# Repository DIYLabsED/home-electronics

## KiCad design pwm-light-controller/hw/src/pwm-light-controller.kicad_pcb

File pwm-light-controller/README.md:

## NAME
### DESC

### REQUIREMENTS

### DESIGN NOTES

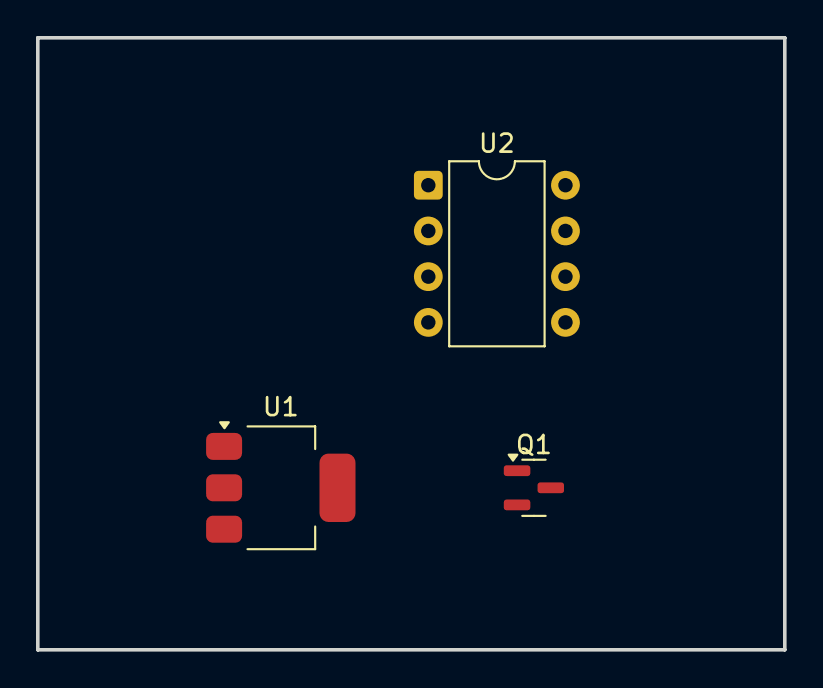
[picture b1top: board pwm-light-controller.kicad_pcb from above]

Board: 2 copper layers, 41.5 x 34.0 mm, 3 parts (0 on the bottom side), 2 nets, no tracks yet.

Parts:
Q1: AO3400A; SOT-23
U1: AMS1117-5.0; SOT-223-3_TabPin2
U2: ATtiny13A-P; DIP-8_W7.62mm

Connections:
+5V: U1.2 (VO), U2.1 (~RESET/PB5), U2.8 (VCC)
GND: Q1.2 (S), U1.1 (GND), U2.4 (GND)

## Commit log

2025-06-09 Create folder for PWM lighting controller
2025-06-09 Remove angle brackets from project README
2025-06-09 Create KiCad project, make power supply circuit in schematic
2025-06-09 Add potentiometers and ATtiny13A
2025-06-09 Add header to switch peak signal
2025-06-09 Add headers for IO
2025-06-09 Change revision to Prototype 1
2025-06-10 Move KiCad files to HW folder
2025-06-10 Add header for external switch
2025-06-10 Export .net file
2025-06-10 Create interactive HTML BOM
2025-06-12 Create PlatformIO project for RP2040-zero clock
2025-06-12 Print millis for tests
2025-06-12 Wait for serial port
2025-06-12 Add upload_port to configuration
2025-06-19 Create schematic
2025-06-19 Change BOD voltage to 1.8 in .ini file
2025-06-19 Remove BOD stuff from .ini
2025-06-20 Add boost converter to schematic
